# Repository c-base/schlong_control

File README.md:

# schlong_control
Controller board for the schlongs

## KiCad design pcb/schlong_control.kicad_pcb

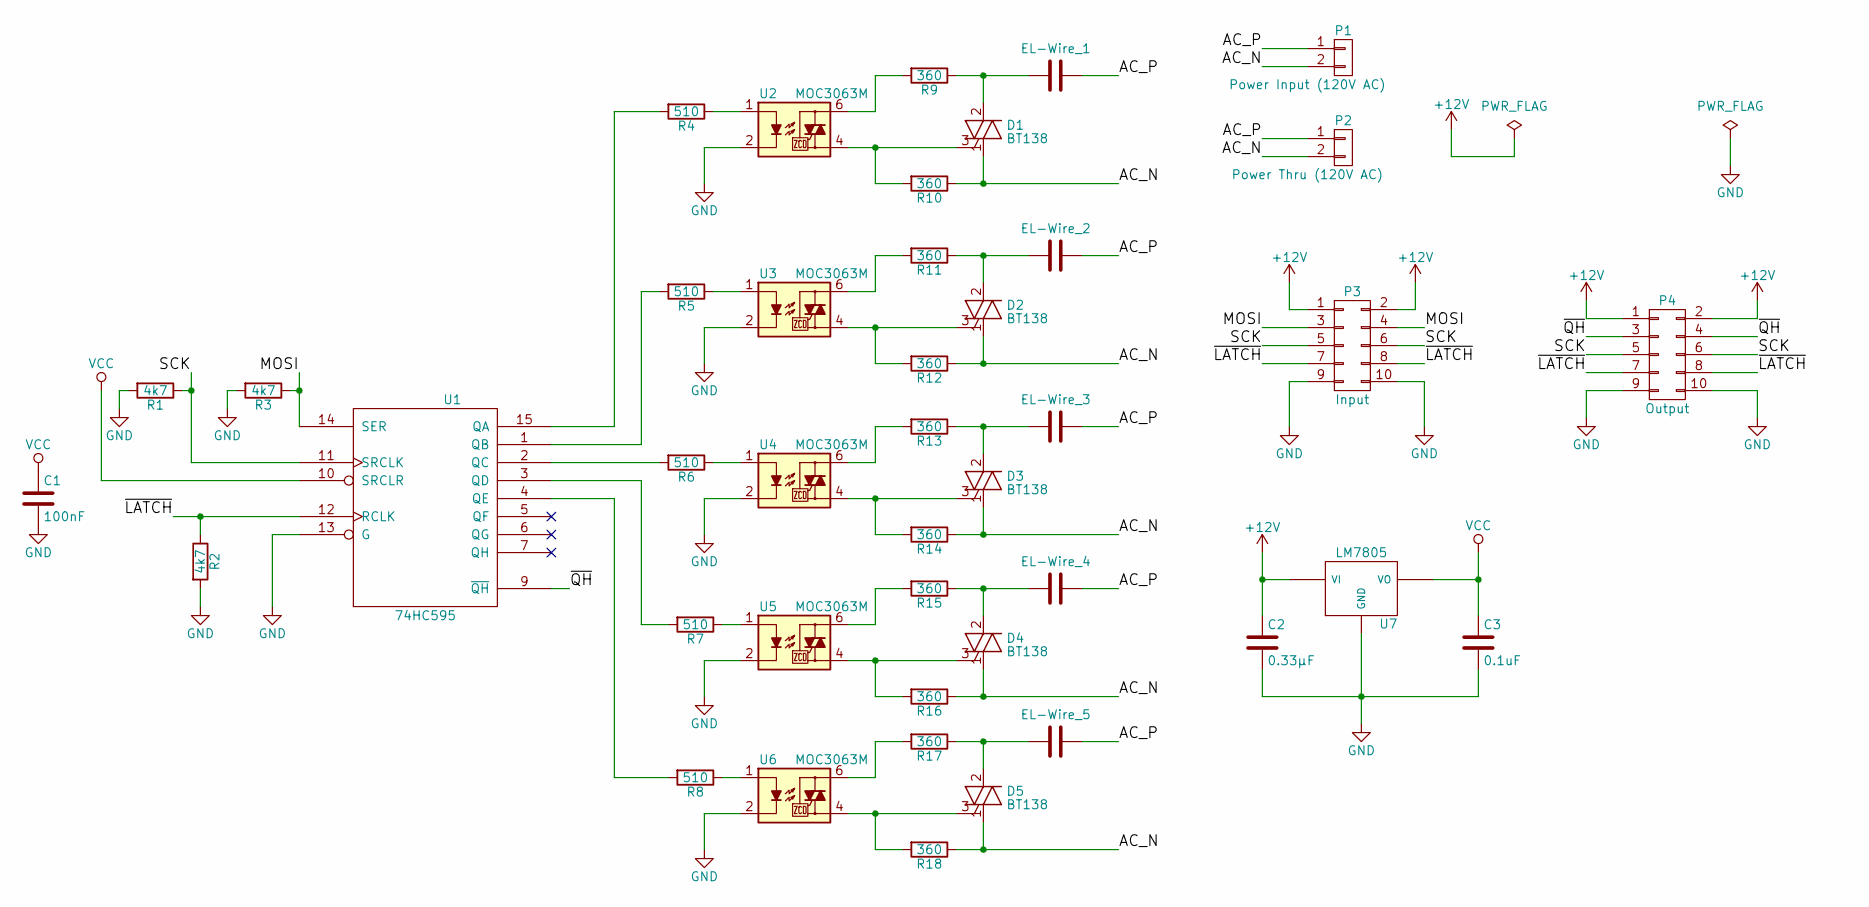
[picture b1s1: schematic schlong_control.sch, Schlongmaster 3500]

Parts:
C1: 100nF; C_Disc_D3.0mm_W1.6mm_P2.50mm
C2: 0.33µF; CP_Radial_D4.0mm_P1.50mm
C3: 0.1uF; CP_Radial_D4.0mm_P1.50mm
D1, D2, D3, D4, D5: BT138; TO-220_Vertical
EL-Wire_1, EL-Wire_2, EL-Wire_3, EL-Wire_4, EL-Wire_5: C; PINHEAD1-2
P1: Power Input (120V AC); TerminalBlock_Phoenix_MKDS1.5-2pol
P2: Power Thru (120V AC); TerminalBlock_Phoenix_MKDS1.5-2pol
P3: Input; IDC_Header_Straight_2x05_Pitch2.54mm
P4: Output; IDC_Header_Straight_2x05_Pitch2.54mm
R1, R2, R3: 4k7; R_Axial_DIN0207_L6.3mm_D2.5mm_P7.62mm_Horizontal
R4, R5, R6, R7, R8: 510; R_Axial_DIN0207_L6.3mm_D2.5mm_P7.62mm_Horizontal
R9, R10, R11, R12, R13, R14, R15, R16, R17, R18: 360; R_Axial_DIN0207_L6.3mm_D2.5mm_P7.62mm_Horizontal
U1: 74HC595; DIP-16_W7.62mm
U2, U3, U4, U5, U6: MOC3063M; DIP-6_W7.62mm
U7: LM7805; TO-220_Vertical

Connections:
+12V: C2.1, P3.1, P3.2, P4.1, P4.2, U7.1 (VI)
/AC_N: D1.1 (T1), D2.1 (T1), D3.1 (T1), D4.1 (T1), D5.1 (T1), P1.2, P2.2, R10.1, R12.1, R14.1, R16.1, R18.1
/AC_P: EL-Wire_1.2, EL-Wire_2.2, EL-Wire_3.2, EL-Wire_4.2, EL-Wire_5.2, P1.1, P2.1
/MOSI: P3.3, P3.4, R3.1, U1.14 (SER)
/SCK: P3.5, P3.6, P4.5, P4.6, R1.1, U1.11 (SRCLK)
/~LATCH: P3.7, P3.8, P4.7, P4.8, R2.1, U1.12 (RCLK)
/~QH: P4.3, P4.4, U1.9 (~QH)
GND: C1.2, C2.2, C3.2, P3.9, P3.10, P4.9, P4.10, R1.2, R2.2, R3.2, U1.8 (GND), U1.13 (G), U2.2, U3.2, U4.2, U5.2, U6.2, U7.2 (GND)
unnamed: D1.2 (T2), EL-Wire_1.1, R9.1
unnamed: D1.3 (G), R10.2, U2.4
unnamed: D2.2 (T2), EL-Wire_2.1, R11.1
unnamed: D2.3 (G), R12.2, U3.4
unnamed: D3.2 (T2), EL-Wire_3.1, R13.1
unnamed: D3.3 (G), R14.2, U4.4
unnamed: D4.2 (T2), EL-Wire_4.1, R15.1
unnamed: D4.3 (G), R16.2, U5.4
unnamed: D5.2 (T2), EL-Wire_5.1, R17.1
unnamed: D5.3 (G), R18.2, U6.4
unnamed: R4.1, U2.1
unnamed: R4.2, U1.15 (QA)
unnamed: R5.1, U3.1
unnamed: R5.2, U1.1 (QB)
unnamed: R6.1, U4.1
unnamed: R6.2, U1.2 (QC)
unnamed: R7.1, U5.1
unnamed: R7.2, U1.3 (QD)
unnamed: R8.1, U6.1
unnamed: R8.2, U1.4 (QE)
unnamed: R9.2, U2.6
unnamed: R11.2, U3.6
unnamed: R13.2, U4.6
unnamed: R15.2, U5.6
unnamed: R17.2, U6.6
VCC: C1.1, C3.1, U1.10 (SRCLR), U1.16 (VCC), U7.3 (VO)

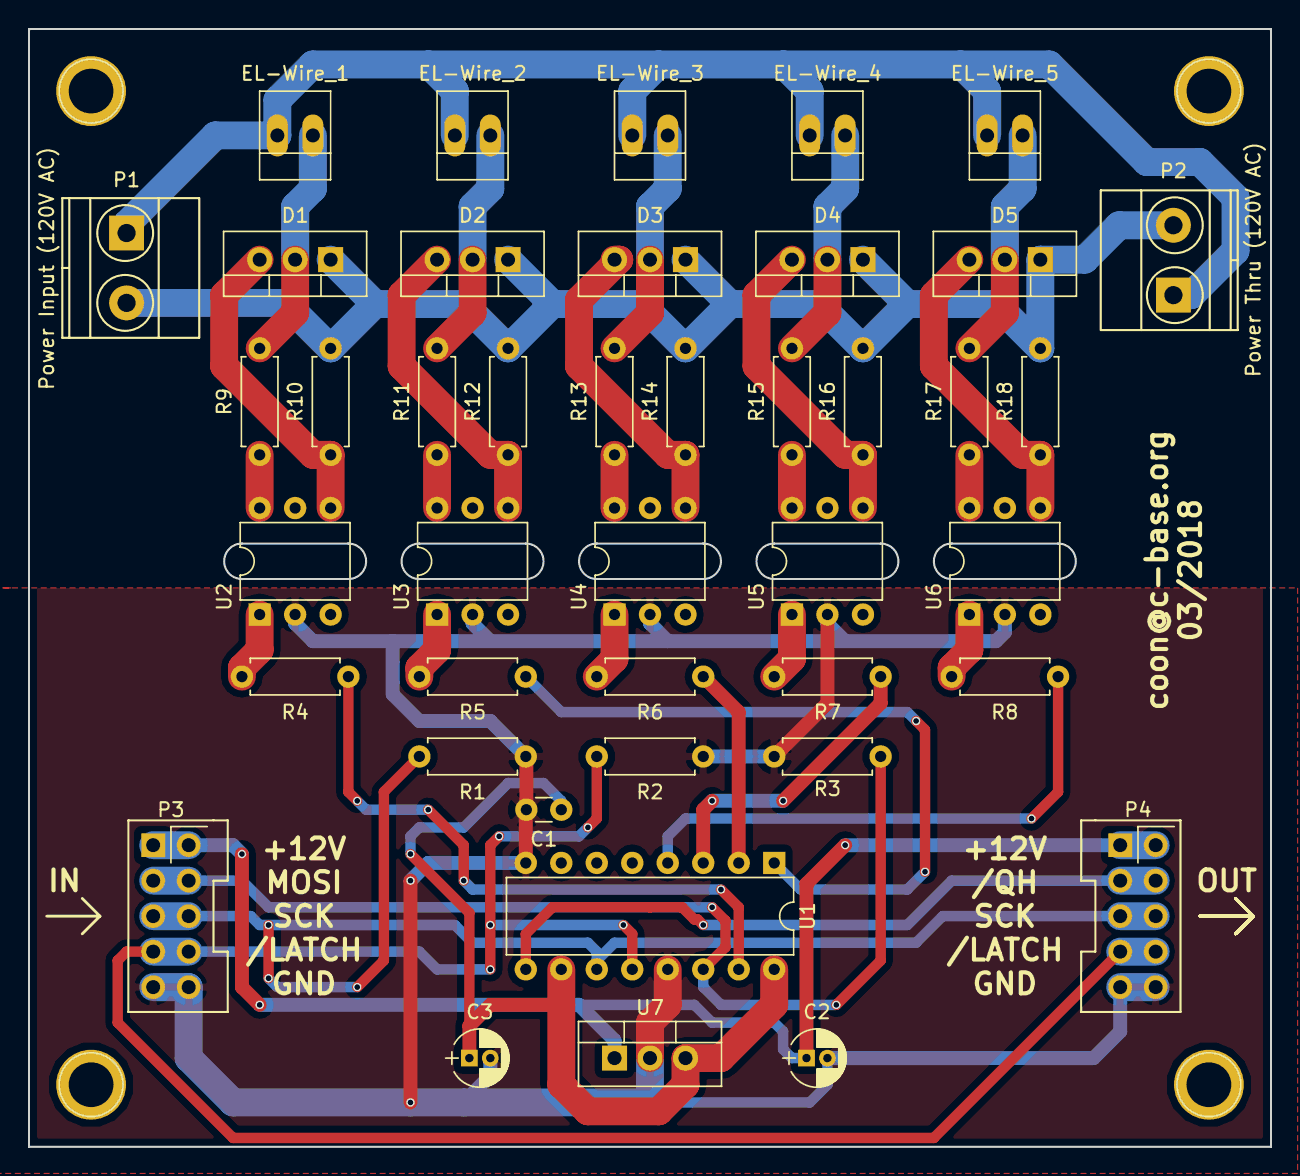
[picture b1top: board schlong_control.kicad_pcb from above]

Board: 2 copper layers, 88.9 x 80.0 mm, 42 parts (0 on the bottom side), 34 nets.

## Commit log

2017-02-18 add schematic
2017-02-18 add data and power connectors / pass ERC
2017-02-27 update circuit
2017-02-27 add resistor to led of each opto triac
2017-03-15 add resistors to neutral, adjust values
2017-03-15 finished circuit
2017-03-17 rev1: use 1k resistors on MOC3063 LED / corrected pinout on BT138
2017-03-19 reduce moc3063 led resistor from 1k to 510R
2017-03-19 update revision no
2017-03-19 add basic pcb layout
2017-04-03 add basic firmware
2017-09-02 enable multiple shlongs for testing
2017-09-02 update pcb
2017-09-02 make pcb more compact
2017-09-02 shinkify pcb even more + little fixes
2017-09-02 routed pcb
2017-09-02 redo routing (seperate logic voltage from AC voltage)
2017-09-03 pcb: improve seperation of low / high voltages
2017-09-03 pcb: shrinkify board
2017-09-03 pcb: add mounting holes
2017-09-04 pcb: adjust footprints of IDC headers
2017-09-04 move caps a little + fix 3D models
2017-09-05 pcb: final optimizations on silk screen
2017-09-05 add gerber files
2018-03-13 add idc header footprint
2018-03-13 rework design
2018-03-14 pcb: add mounting holes + pin descriptions
2018-03-14 add .gitignore
2018-03-14 pcb: move power input / thru description to F.Silk layer
2018-03-14 pcb: finished rerouting
2018-03-14 pcb: fix unconnected pad
2018-03-19 pcb: add mirrored IDC connector footprint for left connector
2018-03-19 pcb: update gerber files
2018-05-19 firmware: rework code for star topology
